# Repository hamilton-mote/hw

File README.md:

# Hamilton open-source hardware

The Hamilton mote (so named for its $10 cost) is a mote based on the ATSAMR21E18A (similar to the MCU present on the Atmel SAMR21XPRO). The low-cost variboard has an accelerometer, a temperature sensor and a light sensor as well as four GPIO pins and an I2C bus. To disseminate sensor data, it uses the 802.15.4 wireless radio built into the SAMR21. The board is not designed to offer huge amounts of GPIO (the [storm](http://storm.rocks) is designed for that), but rather be a platform for low cost wireless sensors that can be deployed en-masse without massive financial outlay.

The primary operating system we support is RIOT-OS. Soon we hope to get support upstream into the RIOT codebase, but for now we will maintain a rebasing fork, broken into feature-branches that can be individually merged on top of upstream.

# Sensor packages

A hamilton board will have a sensor variant designator in its name, for example hamilton-3 or hamilton-1f. This variant indicates the presence of a subset of the following sensors

| Designation  | Description | Part number |
|:-------:|:-------:|:------:|
|  1 | Low-cost temperature sensor | AT30TS74 |
|  2 | Low-cost 3-axis accelerometer | MMA7660 |
|  4 | Light sensor | APDS-9007 |
|  8 | High-precision 3-axis accel/magnetometer | FXOS8700 |
| 10 | Temp / Humidity sensor | HDC1080 |
| 20 | Temp / Radiant sensor | TMP006 |
| 40 | PIR sensor | EKMB110x11x |
| 80 | Ultrasonic ranger | CH201 |
| 100 | High-precision 3-axis accel/magnetometer | LSM303C |
| 200 | Light sensor | ISL29035 |

So far, we have produced three hamilton bundles:

- Hamilton-7 (4+2+1), which costs $10 including the sensors and is designed for cost-sensitive applications
- Hamilton-3C (20+10+8+4), cost TBD, which is designed as an operative temperature sensor with acceleration/magnetometer so it can determine its orientation in the space
- Hamilton-7C (40+20+10+8+4), cost TBD, which adds occupancy (the occupancy sensor doubles the cost of the board)
- Hamilton-330 (200+100+20+10), a replacement for the 3C which has better light sensing and a more readily available accelerometer
- Hamilton-370 (200+100+40+20+10), a replacement for the 7C which adds PIR to the 330

The expected battery life of each of these variants will be put on here when they have been characterised

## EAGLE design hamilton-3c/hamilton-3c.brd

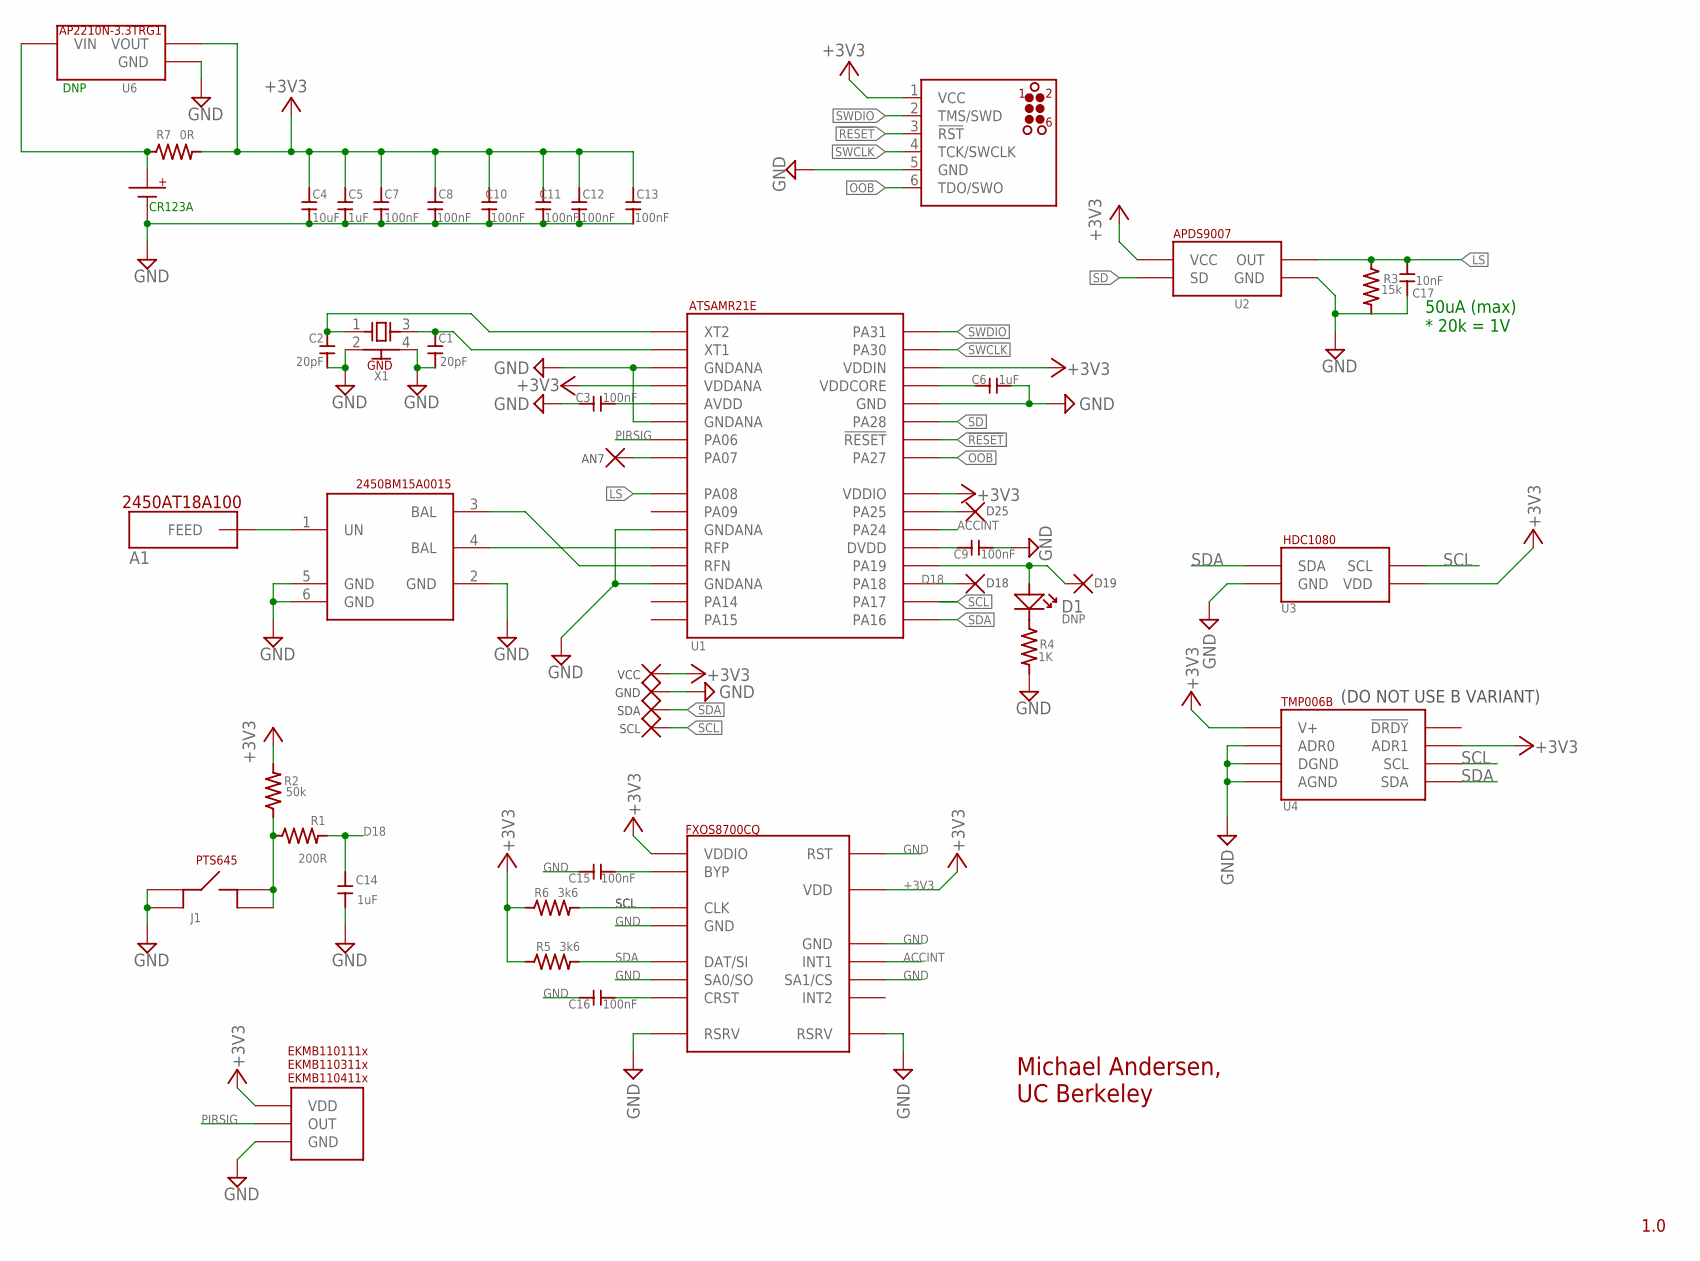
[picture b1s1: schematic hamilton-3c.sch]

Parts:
A1: JOHANSON_ANTENNA2
BT1: 2/3A
C1, C2: 20pF; S0402
C3, C7, C8, C9, C10, C11, C12, C13, C15, C16: 100nF; S0402
C4: 10uF; 0805
C5, C6, C14: 1uF; S0402
C17: 10nF; S0402
D1: DNP; LINE_0603
J1: PTS645
L1: BALUN_JOHANSON
R1: 200R; S0402
R2: 50k; S0402
R3: 15k; S0402
R4: 1K; S0402
R5, R6: 3k6; S0402
R7: 0R; S0402
TP1: D19; TPP
TP2: D18; TPP
TP3: AN7; TPP
TP4: D25; TPP
TP5: VCC; TPP
TP6: GND; TPP
TP7: SDA; TPP
TP8: SCL; TPP
U1: SAMR21; QFN32
U2: APDS9007
U3: HDC1080; WSON_HDC1080
U4: TMP006B; TMP006
U5: ACCEL_FXOS8700CQ; TQFN16
U6: SOT23-3VREG; SOT23
U7: PANASONIC_PIR; PIR
U$1: JLINK_CONNECTWL; TC2030-MCP
X1: XTAL

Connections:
!RESET!: U1.26 (!RESET!), U$1.3 (!RST!)
+3V3: C4.2, C5.P$2, C7.P$1, C8.P$1, C10.P$1, C11.P$1, C12.P$1, C13.P$1, R2.P$1, R5.P$2, R6.P$2, R7.P$1, TP5.P$1, U1.4 (VDDANA), U1.24 (VDDIO), U1.30 (VDDIN), U2.4 (VCC), U3.5 (VDD), U4.A3 (V+), U4.B1 (ADR1), U5.P1 (VDDIO), U5.P14 (VDD), U6.2 (VOUT), U7.VDD, U$1.1 (VCC)
ACCINT: U1.22 (PA24), U5.P11 (INT1)
D18: C14.P$2, R1.P$1, TP2.P$1, U1.19 (PA18)
GND: BT1.NEG (-), C1.P$1, C2.P$1, C3.P$2, C4.1, C5.P$1, C6.P$1, C7.P$2, C8.P$2, C9.P$1, C10.P$2, C11.P$2, C12.P$2, C13.P$2, C14.P$1, C15.P$2, C16.P$2, C17.P$2, J1.3, J1.4, L1.2 (GND), L1.5 (GND), L1.6 (GND), R3.P$1, R4.P$1, TP6.P$1, U1.3 (GNDANA), U1.6 (GNDANA), U1.11 (GNDANA), U1.14 (GNDANA), U1.28 (GND), U2.1 (GND), U3.2 (GND), U4.A1 (DGND), U4.A2 (AGND), U4.C1 (ADR0), U5.P3 (RSRV), U5.P5 (GND), U5.P7 (SA0/SO), U5.P10 (SA1/CS), U5.P12 (GND), U5.P13 (RSRV), U5.P16 (RST), U6.1 (GND), U7.GND, U$1.5 (GND), X1.2 (GND), X1.4 (GND)
LS: C17.P$1, R3.P$2, U1.9 (PA08), U2.3 (OUT)
unnamed: J1.1, J1.2, R1.P$2, R2.P$2
unnamed: L1.3 (BAL), U1.13 (RFN)
unnamed: A1.FEED, L1.1 (UN)
unnamed: C2.P$2, U1.1 (XT2), X1.1 (X1)
unnamed: C6.P$2, U1.29 (VDDCORE)
unnamed: C3.P$1, U1.5 (AVDD)
unnamed: C1.P$2, U1.2 (XT1), X1.3 (X2)
unnamed: TP3.P$1, U1.8 (PA07)
unnamed: TP4.P$1, U1.23 (PA25)
unnamed: C9.P$2, U1.21 (DVDD)
unnamed: D1.P (+), TP1.P$1, U1.20 (PA19)
unnamed: BT1.POS (+), R7.P$2, U6.3 (VIN)
unnamed: L1.4 (BAL), U1.12 (RFP)
unnamed: D1.N (-), R4.P$2
unnamed: C15.P$1, U5.P2 (BYP)
unnamed: C16.P$1, U5.P8 (CRST)
OOB: U1.25 (PA27), U$1.6 (TDO/SWO)
PIRSIG: U1.7 (PA06), U7.OUT
SCL: R6.P$1, TP8.P$1, U1.18 (PA17), U3.6 (SCL), U4.B3 (SCL), U5.P4 (CLK)
SD: U1.27 (PA28), U2.6 (SD)
SDA: R5.P$1, TP7.P$1, U1.17 (PA16), U3.1 (SDA), U4.C3 (SDA), U5.P6 (DAT/SI)
SWCLK: U1.31 (PA30), U$1.4 (TCK/SWCLK)
SWDIO: U1.32 (PA31), U$1.2 (TMS/SWD)

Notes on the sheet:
CR123A
50uA (max) * 20k = 1V
DNP
1.0
Michael Andersen, UC Berkeley
(DO NOT USE B VARIANT)

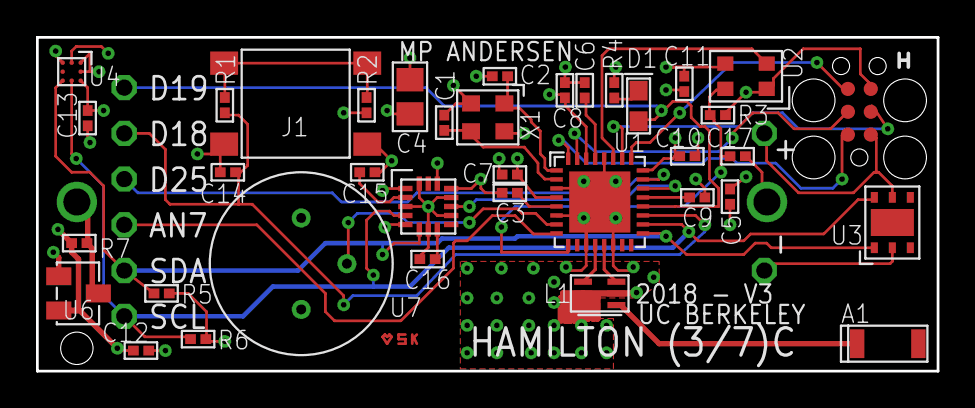
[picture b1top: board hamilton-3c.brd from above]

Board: 4 copper layers, 50.0 x 18.5 mm, 46 parts (1 on the bottom side), 29 nets.

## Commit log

2016-05-22 Add internal versions of hardware
2017-09-28 fix light sensor part number
2017-10-09 Add the hamilton 3C hardware to the same repo

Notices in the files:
parts and their libraries:
storm: ©2009 ROFA.cz
